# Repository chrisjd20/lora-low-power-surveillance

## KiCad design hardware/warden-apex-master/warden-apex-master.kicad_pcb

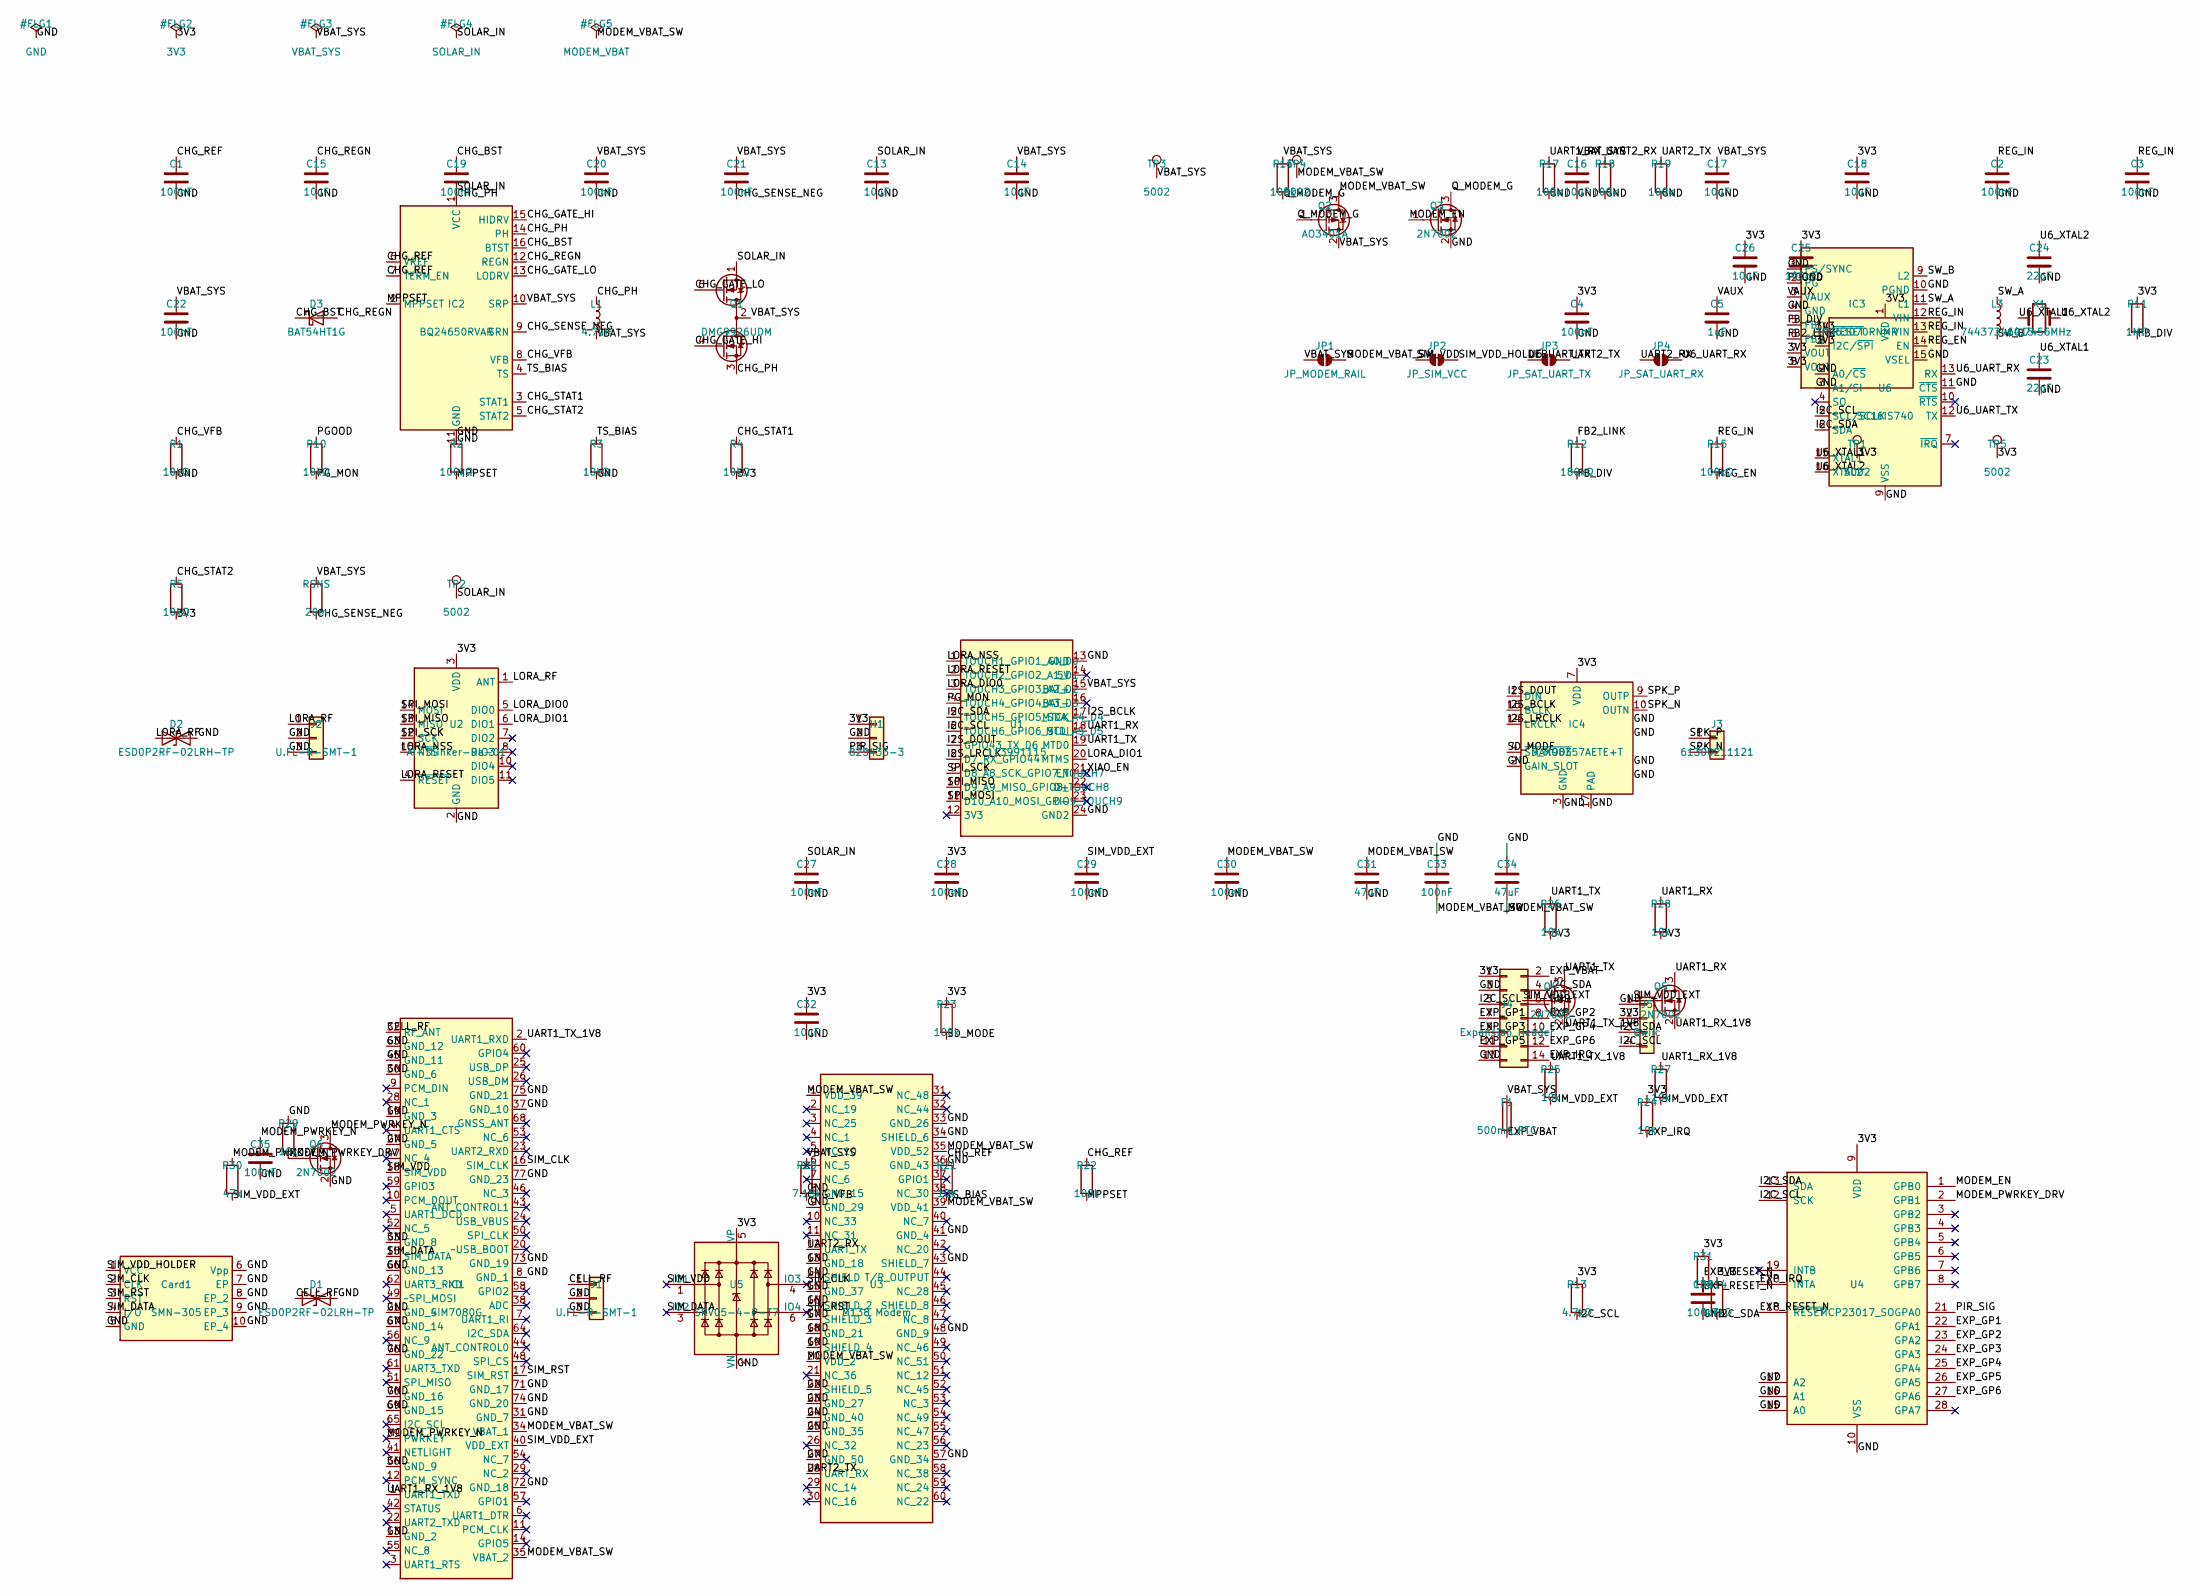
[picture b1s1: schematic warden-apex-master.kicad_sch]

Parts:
C1, C2, C3, C4, C19, C20, C21, C22, C25, C27, C28, C29, C30, C33, C35, C36: 100nF; C_0805_2012Metric
C5: 1uF; C_0805_2012Metric
C13, C14, C15, C16, C17, C18, C26, C32: 10uF; C_0805_2012Metric
C23, C24: 22pF; C_0805_2012Metric
C31, C34: 47uF; C_1206_3216Metric
Card1: SMN-305; SMN-305_Nano_SIM
D1, D2: ESD0P2RF-02LRH-TP; D_SOD-323
D3: BAT54HT1G; D_SOD-323
F1: 500mA_PTC; Fuse_0805_2012Metric
H1: 825433-3; PinHeader_1x03_P2.54mm_Vertical
IC1: SIM7080G; LCC-42_SIM7080G
IC2: BQ24650RVAR; VQFN-16-1EP_3x3mm_P0.5mm_EP1.6x1.6mm
IC3: TPS63070RNMR; TPS63070_RNM0015A
IC4: MAX98357AETE+T; QFN-16-1EP_3x3mm_P0.5mm_EP1.45x1.45mm
J1, J2: U.FL-R-SMT-1; U.FL_Hirose_U.FL-R-SMT-1_Vertical
J3: 61300211121; PinHeader_1x02_P2.54mm_Vertical
J4: Expansion_Header; PinHeader_2x07_P2.54mm_Vertical
J5: Qwiic; JST_SH_SM04B-SRSS-TB_1x04-1MP_P1.00mm_Horizontal
JP1: JP_MODEM_RAIL; SolderJumper-2_P1.3mm_Open_Pad1.0x1.5mm
JP2: JP_SIM_VCC; SolderJumper-2_P1.3mm_Open_Pad1.0x1.5mm
JP3: JP_SAT_UART_TX; SolderJumper-2_P1.3mm_Open_Pad1.0x1.5mm
JP4: JP_SAT_UART_RX; SolderJumper-2_P1.3mm_Open_Pad1.0x1.5mm
L1: 4.7uH; L_Taiyo-Yuden_NR-60xx_HandSoldering
L3: 74437346015; L_APV_ANR4012
Q1: DMG9926UDM; SOT-23-6
Q2: AO3401A; SOT-23
Q3, Q4, Q5, Q6: 2N7002; SOT-23
R1, R3, R4, R5, R10: 10kΩ; R_0805_2012Metric
R2, R15: 100kΩ; R_0805_2012Metric
R11: 1MΩ; R_0805_2012Metric
R12: 180kΩ; R_0805_2012Metric
R13, R14: 4.7kΩ; R_0805_2012Metric
R16, R17, R18, R19, R22, R23: 100k; R_0805_2012Metric
R20: 7.15k; R_0805_2012Metric
R21, R24, R25, R26, R27, R28, R29, R31: 10k; R_0805_2012Metric
R30: 47k; R_0805_2012Metric
RSNS: 20m; R_2512_6332Metric
TP1, TP2, TP3, TP4, TP5: 5002; TestPoint_Pad_D1.5mm
U1: 113991115; XIAO_ESP32S3_SENSE
U2: Ai-Thinker-Ra-01; Ai-Thinker-Ra-01-LoRa
U3: M138 Modem; Swarm_M138
U4: MCP23017_SO; SOIC-28W_7.5x17.9mm_P1.27mm
U5: SRV05-4-P-T7; SOT-23-6
U6: SC16IS740; TSSOP-16_4.4x5mm_P0.65mm
X1: 14.7456MHz; Crystal_SMD_3225-4Pin_3.2x2.5mm

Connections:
/3V3: C4.1, C18.1, C25.1, C26.1, C28.1, C32.1, H1.1, IC3.7 (VOUT), IC3.8 (VOUT), IC4.7 (VDD), IC4.8 (VDD), J4.1, J5.2, R4.2, R5.2, R11.1, R13.1, R14.1, R23.1, R24.1, R26.2, R28.2, R31.1, TP1.1, TP5.1, U2.3 (VDD), U4.9 (VDD), U5.5 (VP), U6.1 (VDD), U6.8 (I2C/~SPI), U6.14 (~RESET)
/CELL_RF: D1.1 (A1), IC1.32 (RF_ANT), J1.1
/CHG_BST: C19.1, D3.1 (K), IC2.16 (BTST)
/CHG_GATE_HI: IC2.15 (HIDRV), Q1.4 (G2)
/CHG_GATE_LO: IC2.13 (LODRV), Q1.6 (G1)
/CHG_PH: C19.2, IC2.14 (PH), L1.1, Q1.3 (S2)
/CHG_REF: C1.1, IC2.6 (VREF), IC2.7 (TERM_EN), R21.1, R22.1
/CHG_REGN: C15.1, D3.2 (A), IC2.12 (REGN)
/CHG_SENSE_NEG: C21.2, IC2.9 (SRN), RSNS.2
/CHG_STAT1: IC2.3 (STAT1), R4.1
/CHG_STAT2: IC2.5 (STAT2), R5.1
/CHG_VFB: IC2.8 (VFB), R1.1, R20.2
/DUMMY_NET_PRESERVE_1: J5.MP
/DUMMY_NET_PRESERVE_2: J5.MP
/DUMMY_NET_PRESERVE_8: U1.12 (3V3)
/DUMMY_NET_PRESERVE_9: U1.14 (5V)
/DUMMY_NET_PRESERVE_10: U1.16 (BAT-)
/DUMMY_NET_PRESERVE_11: U1.22 (D+)
/DUMMY_NET_PRESERVE_12: U1.23 (D-)
/DUMMY_NET_PRESERVE_13: U3.2 (NC_19)
/DUMMY_NET_PRESERVE_14: U3.3 (NC_25)
/DUMMY_NET_PRESERVE_15: U3.4 (NC_1)
/DUMMY_NET_PRESERVE_16: U3.5 (NC_10)
/DUMMY_NET_PRESERVE_17: U3.6 (NC_5)
/DUMMY_NET_PRESERVE_18: U3.7 (NC_6)
/DUMMY_NET_PRESERVE_19: U3.10 (NC_33)
/DUMMY_NET_PRESERVE_20: U3.11 (NC_31)
/DUMMY_NET_PRESERVE_21: U3.21 (NC_36)
/DUMMY_NET_PRESERVE_22: U3.26 (NC_32)
/DUMMY_NET_PRESERVE_23: U3.29 (NC_14)
/DUMMY_NET_PRESERVE_24: U3.30 (NC_16)
/DUMMY_NET_PRESERVE_25: U3.31 (NC_48)
/DUMMY_NET_PRESERVE_26: U3.32 (NC_44)
/DUMMY_NET_PRESERVE_27: U3.37 (GPIO1)
/DUMMY_NET_PRESERVE_28: U3.38 (NC_30)
/DUMMY_NET_PRESERVE_29: U3.40 (NC_7)
/DUMMY_NET_PRESERVE_30: U3.42 (NC_20)
/DUMMY_NET_PRESERVE_31: U3.44 (T/R_OUTPUT)
/DUMMY_NET_PRESERVE_32: U3.45 (NC_28)
/DUMMY_NET_PRESERVE_33: U3.46 (SHIELD_8)
/DUMMY_NET_PRESERVE_34: U3.47 (NC_8)
/DUMMY_NET_PRESERVE_35: U3.49 (NC_46)
/DUMMY_NET_PRESERVE_36: U3.50 (NC_51)
/DUMMY_NET_PRESERVE_37: U3.51 (NC_12)
/DUMMY_NET_PRESERVE_38: U3.52 (NC_45)
/DUMMY_NET_PRESERVE_39: U3.53 (NC_3)
/DUMMY_NET_PRESERVE_40: U3.54 (NC_49)
/DUMMY_NET_PRESERVE_41: U3.55 (NC_47)
/DUMMY_NET_PRESERVE_42: U3.56 (NC_23)
/DUMMY_NET_PRESERVE_43: U3.58 (NC_38)
/DUMMY_NET_PRESERVE_44: U3.59 (NC_24)
/DUMMY_NET_PRESERVE_45: U3.60 (NC_22)
/DUMMY_NET_PRESERVE_50: U2.7 (DIO2)
/DUMMY_NET_PRESERVE_51: U2.8 (DIO3)
/DUMMY_NET_PRESERVE_52: U2.10 (DIO4)
/DUMMY_NET_PRESERVE_53: U2.11 (DIO5)
/DUMMY_NET_PRESERVE_55: U4.3 (GPB2)
/DUMMY_NET_PRESERVE_56: U4.4 (GPB3)
/DUMMY_NET_PRESERVE_57: U4.5 (GPB4)
/DUMMY_NET_PRESERVE_58: U4.6 (GPB5)
/DUMMY_NET_PRESERVE_59: U4.7 (GPB6)
/DUMMY_NET_PRESERVE_60: U4.8 (GPB7)
/DUMMY_NET_PRESERVE_61: U4.11 (NC)
/DUMMY_NET_PRESERVE_62: U4.14 (NC)
/DUMMY_NET_PRESERVE_63: U4.19 (INTB)
/DUMMY_NET_PRESERVE_64: U4.28 (GPA7)
/DUMMY_NET_PRESERVE_65: U6.4 (SO)
/DUMMY_NET_PRESERVE_66: U6.7 (~IRQ)
/DUMMY_NET_PRESERVE_67: U6.10 (~RTS)
/DUMMY_NET_PRESERVE_68: IC1.3 (UART1_RTS)
/DUMMY_NET_PRESERVE_69: IC1.4 (UART1_CTS)
/DUMMY_NET_PRESERVE_70: IC1.5 (UART1_DCD)
/DUMMY_NET_PRESERVE_71: IC1.6 (UART1_DTR)
/DUMMY_NET_PRESERVE_72: IC1.7 (UART1_RI)
/DUMMY_NET_PRESERVE_73: IC1.9 (PCM_DIN)
/DUMMY_NET_PRESERVE_74: IC1.10 (PCM_DOUT)
/DUMMY_NET_PRESERVE_75: IC1.11 (PCM_CLK)
/DUMMY_NET_PRESERVE_76: IC1.12 (PCM_SYNC)
/DUMMY_NET_PRESERVE_77: IC1.14 (GPIO5)
/DUMMY_NET_PRESERVE_78: IC1.20 (~USB_BOOT)
/DUMMY_NET_PRESERVE_79: IC1.22 (UART2_TXD)
/DUMMY_NET_PRESERVE_80: IC1.23 (UART2_RXD)
/DUMMY_NET_PRESERVE_81: IC1.24 (USB_VBUS)
/DUMMY_NET_PRESERVE_82: IC1.25 (USB_DP)
/DUMMY_NET_PRESERVE_83: IC1.26 (USB_DM)
/DUMMY_NET_PRESERVE_84: IC1.28 (NC_1)
/DUMMY_NET_PRESERVE_85: IC1.29 (NC_2)
/DUMMY_NET_PRESERVE_86: IC1.38 (ADC)
/DUMMY_NET_PRESERVE_87: IC1.41 (NETLIGHT)
/DUMMY_NET_PRESERVE_88: IC1.42 (STATUS)
/DUMMY_NET_PRESERVE_111: X1.3
/DUMMY_NET_PRESERVE_112: X1.4
/EXP_GP1: J4.7, U4.22 (GPA1)
/EXP_GP2: J4.8, U4.23 (GPA2)
/EXP_GP3: J4.9, U4.24 (GPA3)
/EXP_GP4: J4.10, U4.25 (GPA4)
/EXP_GP5: J4.11, U4.26 (GPA5)
/EXP_GP6: J4.12, U4.27 (GPA6)
/EXP_IRQ: J4.14, R24.2, U4.20 (INTA)
/EXP_RESET_N: C36.1, R31.2, U4.18 (~RESET)
/EXP_VBAT: F1.2, J4.2
/FB2_LINK: IC3.6 (FB2), R12.1
/FB_DIV: IC3.5 (FB), R11.2, R12.2
/I2C_SCL: J4.5, J5.4, R13.2, U1.6 (TOUCH6_GPIO6_SCL_A5_D5), U4.12 (SCK), U6.5 (SCL/SCLK)
/I2C_SDA: J4.4, J5.3, R14.2, U1.5 (TOUCH5_GPIO5_SDA_A4_D4), U4.13 (SDA), U6.6 (SDA)
/I2S_BCLK: IC4.16 (BCLK), U1.17 (MTCK)
/I2S_DOUT: IC4.1 (DIN), U1.7 (GPIO43_TX_D6)
/I2S_LRCLK: IC4.14 (LRCLK), U1.8 (D7_RX_GPIO44)
/LORA_DIO0: U1.3 (TOUCH3_GPIO3_A2_D2), U2.5 (DIO0)
/LORA_DIO1: U1.20 (MTMS), U2.6 (DIO1)
/LORA_NSS: U1.1 (TOUCH1_GPIO1_A0_D0), U2.15 (~NSS)
/LORA_RESET: U1.2 (TOUCH2_GPIO2_A1_D1), U2.4 (~RESET)
/LORA_RF: D2.1 (A1), J2.1, U2.1 (ANT)
/MODEM_EN: Q3.1 (G), U4.1 (GPB0)
/MODEM_PWRKEY_DRV: Q6.1 (G), R29.2, U4.2 (GPB1)
/MODEM_PWRKEY_N: C35.1, IC1.39 (PWRKEY), Q6.3 (D), R30.1
/MODEM_VBAT_SW: C30.1, C31.1, C33.2, C34.2, IC1.34 (VBAT_1), IC1.35 (VBAT_2), JP1.2 (B), Q2.3 (D), TP4.1, U3.1 (VDD_39), U3.20 (VDD_2), U3.35 (VDD_52), U3.39 (VDD_41)
/MPPSET: IC2.2 (MPPSET), R2.2, R22.2
/PGOOD: IC3.2 (PG), R10.1
/PG_MON: R10.2, U1.4 (TOUCH4_GPIO4_A3_D3)
/PIR_SIG: H1.3, U4.21 (GPA0)
/Q_MODEM_G: Q2.1 (G), Q3.3 (D), R16.2
/REG_EN: IC3.14 (EN), R15.2
/REG_IN: C2.1, C3.1, IC3.12 (VIN), IC3.13 (VIN), R15.1
/SD_MODE: IC4.4 (~SD_MODE), R23.2
/SIM_CLK: Card1.2 (CLK), IC1.16 (SIM_CLK), U5.4 (IO3)
/SIM_DATA: Card1.4 (I/O), IC1.15 (SIM_DATA), U5.3 (IO2)
/SIM_RST: Card1.3 (RST), IC1.17 (SIM_RST), U5.6 (IO4)
/SIM_VDD: IC1.18 (SIM_VDD), JP2.1 (A), U5.1 (IO1)
/SIM_VDD_EXT: C29.1, IC1.40 (VDD_EXT), Q4.1 (G), Q5.1 (G), R25.2, R27.2, R30.2
/SIM_VDD_HOLDER: Card1.1 (VCC), JP2.2 (B)
/SOLAR_IN: C13.1, C27.1, IC2.1 (VCC), Q1.1 (D1), TP2.1
/SPI_MISO: U1.10 (D9_A9_MISO_GPIO8_TOUCH8), U2.13 (MISO)
/SPI_MOSI: U1.11 (D10_A10_MOSI_GPIO9_TOUCH9), U2.14 (MOSI)
/SPI_SCK: U1.9 (D8_A8_SCK_GPIO7_TOUCH7), U2.12 (SCK)
/SPK_N: IC4.10 (OUTN), J3.2
/SPK_P: IC4.9 (OUTP), J3.1
/SW_A: IC3.11 (L1), L3.1
/SW_B: IC3.9 (L2), L3.2
/TS_BIAS: IC2.4 (TS), R3.1, R21.2
/U6_UART_RX: JP4.2 (B), U6.13 (RX)
/U6_UART_TX: JP3.1 (A), U6.12 (TX)
/U6_XTAL1: C23.1, U6.15 (XTAL1), X1.1
/U6_XTAL2: C24.1, U6.16 (XTAL2), X1.2
/UART1_RX: Q5.3 (D), R17.1, R28.1, U1.18 (MTDI)
/UART1_RX_1V8: IC1.1 (UART1_TXD), Q5.2 (S), R27.1
/UART1_TX: Q4.3 (D), R26.1, U1.19 (MTD0)
/UART1_TX_1V8: IC1.2 (UART1_RXD), Q4.2 (S), R25.1
/UART2_RX: JP4.1 (A), R18.1, U3.12 (UART_TX)
/UART2_TX: JP3.2 (B), R19.1, U3.28 (UART_RX)
/VAUX: C5.1, IC3.3 (VAUX)
/VBAT_SYS: C14.1, C16.1, C17.1, C20.1, C21.1, C22.1, F1.1, IC2.10 (SRP), JP1.1 (A), L1.2, Q1.2 (S1/D2), Q1.5 (S1/D2), Q2.2 (S), R16.1, R20.1, RSNS.1, TP3.1, U1.15 (BAT+)
/XIAO_EN: U1.21 (EN)

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
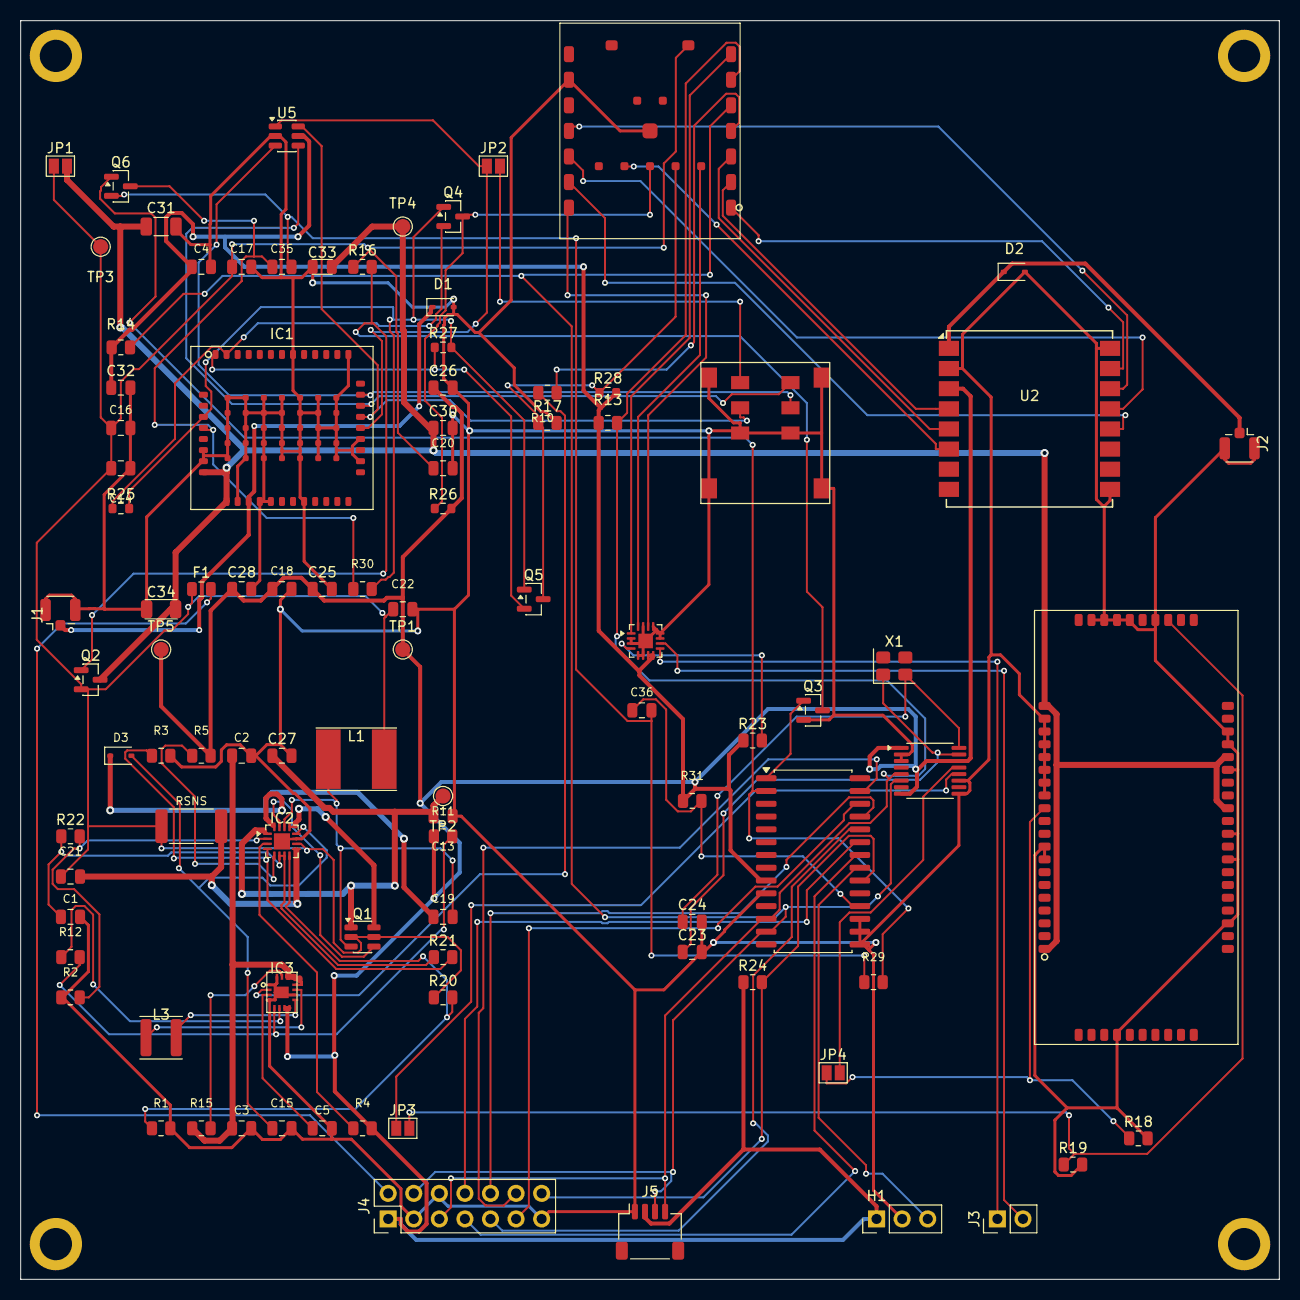
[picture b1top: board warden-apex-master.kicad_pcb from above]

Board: 4 copper layers, 125.0 x 125.0 mm, 100 parts (0 on the bottom side), 74 nets.

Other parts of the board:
MH1, MH2, MH3, MH4: MountingHole

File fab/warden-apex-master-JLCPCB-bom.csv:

Comment,Designator,Footprint,LCSC Part #
100nF,"C1,C2,C3,C4,C5,C19,C20,C21,C22",C_0805_2012Metric,
10uF,"C13,C14,C15,C16,C17,C18",C_0805_2012Metric,
SMN-305,Card1,SMN-305_Nano_SIM,C266890
ESD0P2RF-02LRH-TP,"D1,D2",D_SOD-323,C907863
BAT54HT1G,D3,D_SOD-323,
825433-3,H1,PinHeader_1x03_P2.54mm_Vertical,C306148
SIM7080G,IC1,LCC-42_SIM7080G,
BQ24650RVAR,IC2,VQFN-16-1EP_3x3mm_P0.5mm_EP1.6x1.6mm,
TPS63070RNMR,IC3,QFN-15-1EP_3x4mm_P0.5mm_EP1.45x2.45mm,
MAX98357AETE+T,IC4,QFN-16-1EP_3x3mm_P0.5mm_EP1.45x1.45mm,
U.FL-R-SMT-1,"J1,J2",U.FL_Hirose_U.FL-R-SMT-1_Vertical,
61300211121,J3,PinHeader_1x02_P2.54mm_Vertical,
4.7uH,L1,L_Taiyo-Yuden_NR-60xx_HandSoldering,
74437346015,L3,L_APV_ANR4012,
DMG9926UDM,Q1,SOT-23-6,
10kΩ,"R1,R3,R4,R5,R10",R_0805_2012Metric,
100kΩ,"R2,R15",R_0805_2012Metric,
1MΩ,R11,R_0805_2012Metric,
180kΩ,R12,R_0805_2012Metric,
4.7kΩ,"R13,R14",R_0805_2012Metric,
20m,RSNS?,R_2512_6332Metric,
5002,"TP1,TP2,TP3,TP4,TP5",TestPoint_Pad_D1.5mm,
113991115,U1,XIAO_ESP32S3_SENSE,
Ai-Thinker-Ra-01,U2,Ai-Thinker-Ra-01-LoRa,
M138 Modem,U3,Swarm_M138,
MCP23017_SO,U4,SOIC-28W_7.5x17.9mm_P1.27mm,
SRV05-4-P-T7,U5,SOT-23-6,

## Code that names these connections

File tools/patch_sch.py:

import sys
import uuid

def gen_uuid():
    return str(uuid.uuid4())

def make_label(name, x, y):
    return f'(label "{name}" (at {x} {y} 0) (effects (font (size 1.27 1.27)) (justify left bottom)))'

def make_symbol(ref, val, lib_id, footprint, x, y, uid):
    return f'''(symbol (lib_id "{lib_id}") (at {x} {y} 0) (unit 1) (in_bom yes) (on_board yes) (dnp no) (uuid "{uid}")
  (property "Reference" "{ref}" (at {x} {y-2.54} 0) (effects (font (size 1.27 1.27))))
  (property "Value" "{val}" (at {x} {y+2.54} 0) (effects (font (size 1.27 1.27))))
  (property "Footprint" "{footprint}" (at {x} {y} 0) (effects (font (size 1.27 1.27)) (hide yes)))
  (property "Datasheet" "~" (at {x} {y} 0) (effects (font (size 1.27 1.27)) (hide yes)))
  (instances (project "project" (path "/" (reference "{ref}") (unit 1))))
)'''

with open('hardware/warden-apex-master/warden-apex-master.kicad_sch', 'r') as f:
    sch = f.read()

sch = sch.strip()
if sch.endswith(')'):
    sch = sch[:-1]

items = []
items.append(make_label("MODEM_PWRKEY_N", 88.9, 279.4))
items.append(make_label("MODEM_PWRKEY_N", 215.9, 158.75))

items.append(make_label("SIM_VDD", 139.7, 251.46))
items.append(make_label("SIM_DATA", 139.7, 256.54))
items.append(make_label("SIM_CLK", 165.1, 251.46))
items.append(make_label("SIM_RST", 165.1, 256.54))

items.append(make_symbol("Q4", "2N7002", "Transistor_FET:2N7002", "Package_TO_SOT_SMD:SOT-23", 300, 200, gen_uuid()))
items.append(make_label("VDD_EXT", 294.92, 200.0))
items.append(make_label("UART1_TX_1V8", 302.54, 205.08))
items.append(make_label("UART1_TX", 302.54, 194.92))

items.append(make_symbol("Q5", "2N7002", "Transistor_FET:2N7002", "Package_TO_SOT_SMD:SOT-23", 320, 200, gen_uuid()))
items.append(make_label("VDD_EXT", 314.92, 200.0))
items.append(make_label("UART1_RX_1V8", 322.54, 205.08))
items.append(make_label("UART1_RX", 322.54, 194.92))

items.append(make_symbol("R25", "10k", "Device:R", "Resistor_SMD:R_0805_2012Metric", 300, 215, gen_uuid()))
items.append(make_label("UART1_TX_1V8", 300.0, 211.19))
items.append(make_label("VDD_EXT", 300.0, 218.81))

items.append(make_symbol("R26", "10k", "Device:R", "Resistor_SMD:R_0805_2012Metric", 300, 185, gen_uuid()))
items.append(make_label("UART1_TX", 300.0, 181.19))
items.append(make_label("3V3", 300.0, 188.81))

items.append(make_symbol("R27", "10k", "Device:R", "Resistor_SMD:R_0805_2012Metric", 320, 215, gen_uuid()))
items.append(make_label("UART1_RX_1V8", 320.0, 211.19))
items.append(make_label("VDD_EXT", 320.0, 218.81))

items.append(make_symbol("R28", "10k", "Device:R", "Resistor_SMD:R_0805_2012Metric", 320, 185, gen_uuid()))
items.append(make_label("UART1_RX", 320.0, 181.19))
items.append(make_label("3V3", 320.0, 188.81))

sch += "\n  " + "\n  ".join(items) + "\n)"

with open('hardware/warden-apex-master/warden-apex-master.kicad_sch', 'w') as f:
    f.write(sch)
    
print("Schematic patched.")

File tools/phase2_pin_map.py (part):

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    * SYMBOL_CHOICE    — KiCad library:symbol per Flux cell
    * NET_RENAME       — unnamed Flux "Net 1..5" → meaningful charger names
    * ADDED_PARTS      — L1 (charger inductor) and RSNS (sense resistor)
    * ADDED_NET_NODES  — extra pin-net attachments for L1, RSNS, LORA_DIO1 fix
    * ZONES            — component placement coordinates by functional zone
    * NO_CONNECTS      — pins to explicitly flag as NC after wiring
    * POWER_FLAG_NETS  — nets that must carry a PWR_FLAG for ERC
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#   L1 bridges CHG_PH and VBAT_SYS
#   RSNS bridges VBAT_SYS (SRP side) and CHG_SENSE_NEG (SRN side)
ADDED_NET_NODES = [
    ("CHG_PH",        "L1",   "1"),  # Device:L pin 1
    ("VBAT_SYS",      "L1",   "2"),  # Device:L pin 2
    ("VBAT_SYS",      "RSNS", "1"),  # Device:R pin 1 ← SRP side
    ("CHG_SENSE_NEG", "RSNS", "2"),  # Device:R pin 2 ← SRN side
    ("LORA_DIO1",     "U1",   "20"), # XIAO MTMS (pin 20)
]


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    # GPIOs / AUX lines. ~40 pins. See list_unconnected_pins() below.
    # MCP23017 (U4) — unused GPB*, INTA/INTB, A2
    # MAX98357A (IC4) — none; all strapped to GND already
    # Swarm M138 (U3) — most NC + T/R_OUTPUT + GPIO1
]
# The list is built dynamically by compute_no_connects() based on the
# netlist at build time (fewer chances of drift).
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
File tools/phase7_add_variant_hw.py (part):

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# Library pin 1 "GPB0" is at (17.78, 20.32) in MCP23017_SO symbol; with
# our placement that maps to abs (373.38, 233.68). Pin 1 currently has
# a no_connect flag (GPB0 is unused in Phase 2). Phase 7 removes that
# NC flag and drops a MODEM_EN label at that position.
EXTRA_LABEL_ENDPOINTS: list[tuple[str, float, float]] = [
    ("MODEM_EN", 373.38, 233.68),
]

# no_connect flags to REMOVE (at these absolute positions). Required
# because MODEM_EN now lands on MCP23017 pin 1 which was previously
# strapped as NC in Phase 2.
REMOVE_NO_CONNECT_AT: list[tuple[float, float]] = [
    (373.38, 233.68),
]

# One existing SIM_VDD label is near the Nano-SIM holder Card1 (at 38.10,
# 248.92). Phase 7 renames that ONE label to SIM_VDD_HOLDER so the new
# JP2 jumper is in series between the SIM7080G and the Nano-SIM holder.
RENAME_LABEL_AT: list[tuple[float, float, str, str]] = [
    (38.10, 248.92, "SIM_VDD", "SIM_VDD_HOLDER"),
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        print("Phase 7 marker already present — nothing to do.")
        return 0

    # 0) Selective SIM_VDD label rename (one specific label, not all).
    count, text = rename_label_at(text, RENAME_LABEL_AT)
    print(f"Renamed {count} specific labels (SIM_VDD -> SIM_VDD_HOLDER near Card1)")

    # 1) Bulk net rename
    if "MODEM_VBAT" in NET_RENAMES:
        before = text.count('(label "MODEM_VBAT"')
        for old, new in NET_RENAMES.items():
            text = text.replace(f'(label "{old}"', f'(label "{new}"')
        after  = text.count('(label "MODEM_VBAT_SW"')
        print(f"Renamed MODEM_VBAT -> MODEM_VBAT_SW on {before} labels (now {after})")

    # 2) Remove obsolete no_connect flags where we now need a real label
    text, removed = remove_nc_at(text, REMOVE_NO_CONNECT_AT)
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
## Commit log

2026-04-17 werk it
2026-04-17 Update warden-apex design with new components and net classifications. Added multiple capacitors (C27, C28, C29, C30, C31, C32) and a resistor (R23) to the schematic and PCB. Updated net classes for 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
2026-04-17 Update warden-apex design with new components including F1 (500mA PTC fuse), J4 (Expansion Header), and J5 (Qwiic connector). Adjusted resistor values and footprints for C31 and R24. Updated BOM file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
2026-04-17 Update warden-apex design with new resistor values and components. Changed C5 to 1uF and added resistors R20 (7.15k) and R21 (10k) to the schematic. Updated BOM files to reflect these changes and adj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
2026-04-17 Update warden-apex design with revised net names and routing adjustments. Renamed net SIM_VDD_HOLDER to SIM_VDD_EXT and updated associated nodes. Adjusted timestamps in Gerber files and documentation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
2026-04-18 Remove obsolete BOM and DRC files from the warden-apex design. This cleanup eliminates outdated component references and design rule check data, streamlining the project structure.
2026-04-18 Update warden-apex design for Phase 21 SIM7080 repair. Adjusted BOM files to include new capacitor C33 and updated component placements for C34. Revised Gerber files with new timestamps and corrected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
2026-04-18 Update warden-apex design for Phase 22 power-rail hardening. Enhanced README.md with detailed changes, including widened power-net segments and added ground stitching. Updated Gerber files with new t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
2026-04-18 Update warden-apex design with new components and routing improvements. Added capacitors C35 and C36, and resistor R25 to the BOM files. Adjusted Gerber files with updated timestamps and ensured UART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
2026-04-18 Refine warden-apex design by removing unused components C35, C36, and R25 from BOM files. Update README.md to reflect UART1 routing changes, now directly connecting between U1 and IC1. Revise Gerber 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
2026-04-18 Refactor LCC-42_SIM7080G footprint by renaming pads 8 to 3-7 and 9-26 for improved clarity and organization. Adjusted pad attributes while maintaining existing design specifications.
2026-04-18 Update warden-apex design to Phase 24 live state. Enhanced README.md to clarify current design status, noting that the snapshot is not yet production-ready. Adjusted BOM files to include additional r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
2026-04-18 Remove obsolete ERC report file and update README.md to reflect the current post-repair release snapshot. Adjusted DRC results to indicate zero violations and unconnected items, confirming readiness 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
2026-04-18 Update warden-apex design to Phase 24 live state, enhancing README.md to clarify current design status and confirming readiness for fabrication with zero violations and unconnected items. Adjusted BO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
2026-04-19 Refactor warden-custom symbol by updating footprint reference and renaming pins for clarity. Adjusted pin names to better reflect their functions, enhancing overall readability and usability of the s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
2026-04-19 Update warden-apex design with new components and adjustments to BOM files. Added capacitors C35 and C36, and resistor R30, while updating references for existing components. Revised Gerber files wit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
2026-04-19 Update warden-apex design with revised DRC and ERC results, reflecting current warnings and violations. Adjusted README.md to clarify design status and known caveats. Updated Gerber files with new ti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
2026-04-19 Adjust component placements in warden-apex design for improved layout. Updated coordinates for multiple footprints, including capacitors and resistors, to enhance overall PCB design integrity. Ensure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
2026-04-19 Update warden-apex PCB layout with adjusted component placements and footprint coordinates for improved design accuracy. Modified positions of pin headers and various properties to enhance clarity an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
2026-04-19 Enhance warden-apex PCB layout by adding multiple segments and vias to improve connectivity and routing for net 1 and net 2. Updated trace widths and layer assignments to optimize design performance.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
